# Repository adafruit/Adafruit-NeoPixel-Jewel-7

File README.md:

# Adafruit NeoPixel Jewel containing 7 NeoPixels

<a href="http://www.adafruit.com/products/2226"><br/>
Click here to purchase one from the Adafruit shop</a>

We fit seven of our tiny 5050 (5mm x 5mm) smart RGB LEDs onto a beautiful, round PCB with mounting holes and a chainable design to create what we think is our most elegant (and evening-wear appropriate) NeoPixel board yet.

Use only one microcontroller pin to control as many as you can chain together! Each LED is addressable as the driver chip is inside the LED. Each one has ~18mA constant current drive so the color will be very consistent even if the voltage varies, and no external choke resistors are required making the design slim. Power the whole thing with 5VDC and you're ready to rock.

PCB files for Adafruit NeoPixel Jewel with 7 NeoPixel LEDs

For more details, check out the product page at

-----> https://www.adafruit.com/product/2226

### License

Adafruit invests time and resources providing this open source design, please support Adafruit and open-source hardware by purchasing products from [Adafruit](https://www.adafruit.com)!

All text above must be included in any redistribution

Designed by Limor Fried/Ladyada for Adafruit Industries.
Creative Commons Attribution/Share-Alike, all text above must be included in any redistribution. 
See license.txt for additional information.

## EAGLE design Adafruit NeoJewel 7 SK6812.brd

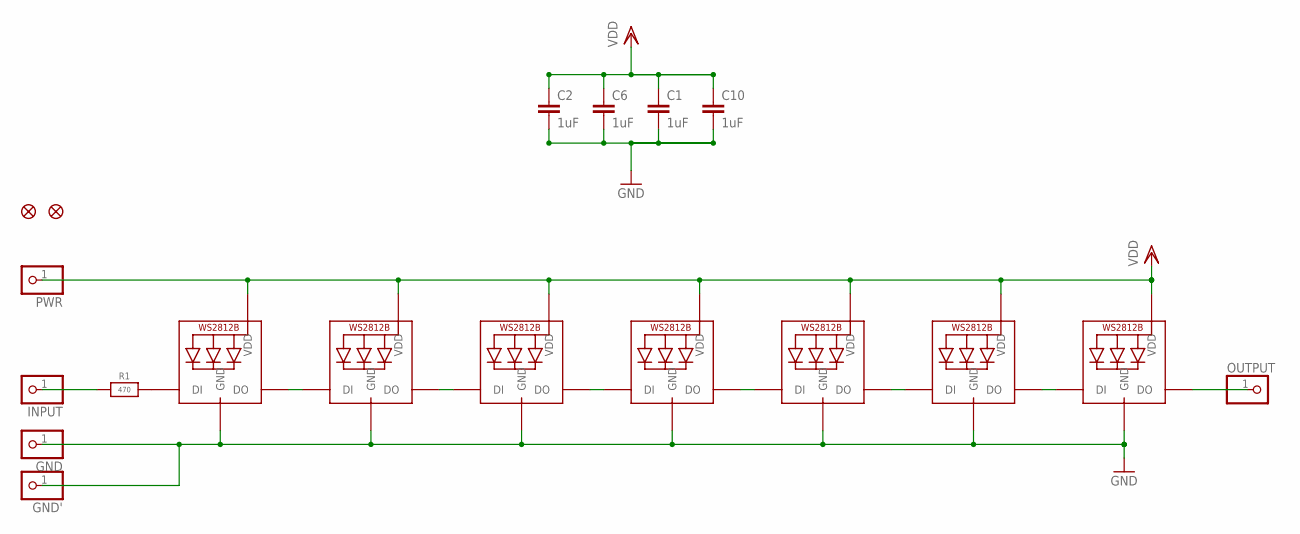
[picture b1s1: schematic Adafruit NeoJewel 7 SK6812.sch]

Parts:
C1, C2, C6, C10: 1uF; C0603
FID1, FID2: FIDUCIAL_1MM
GND: PINHD-1X1CB; 1X01-CLEANBIG
GND': PINHD-1X1CB; 1X01-CLEANBIG
INPUT: PINHD-1X1CB; 1X01-CLEANBIG
LED1, LED2, LED3, LED4, LED5, LED6, LED7: WS2812B_5050N; WS2812B-NARROW
OUTPUT: PINHD-1X1CB; 1X01-CLEANBIG
PWR: PINHD-1X1CB; 1X01-CLEANBIG
R1: 470; 0603-NO

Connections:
GND: C1.2, C2.2, C6.2, C10.2, GND.1, GND'.1, LED1.3-GND (GND), LED2.3-GND (GND), LED3.3-GND (GND), LED4.3-GND (GND), LED5.3-GND (GND), LED6.3-GND (GND), LED7.3-GND (GND)
unnamed: LED1.2-DOUT (DO), LED2.4-DIN (DI)
unnamed: LED2.2-DOUT (DO), LED3.4-DIN (DI)
unnamed: LED3.2-DOUT (DO), LED4.4-DIN (DI)
unnamed: LED4.2-DOUT (DO), LED5.4-DIN (DI)
unnamed: LED5.2-DOUT (DO), LED6.4-DIN (DI)
unnamed: LED6.2-DOUT (DO), LED7.4-DIN (DI)
unnamed: LED7.2-DOUT (DO), OUTPUT.1
unnamed: LED1.4-DIN (DI), R1.2
unnamed: INPUT.1, R1.1
VDD: C1.1, C2.1, C6.1, C10.1, LED1.1-VDD (VDD), LED2.1-VDD (VDD), LED3.1-VDD (VDD), LED4.1-VDD (VDD), LED5.1-VDD (VDD), LED6.1-VDD (VDD), LED7.1-VDD (VDD), PWR.1

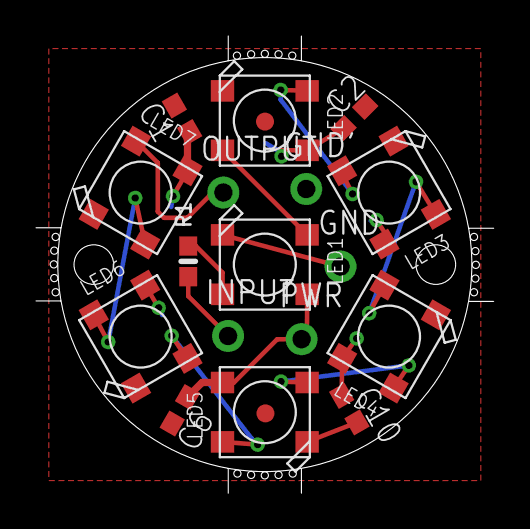
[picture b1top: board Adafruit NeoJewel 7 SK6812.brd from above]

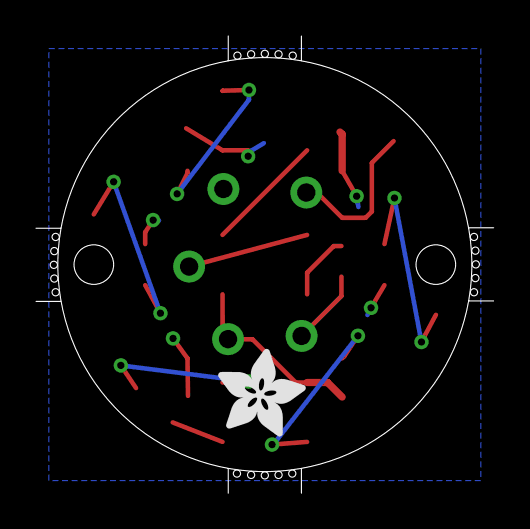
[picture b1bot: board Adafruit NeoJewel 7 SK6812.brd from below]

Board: 2 copper layers, 23.0 x 23.0 mm, 30 parts (7 on the bottom side), 11 nets.

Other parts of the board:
PLABEL0: PLABEL0
PLABEL1: PLABEL1
PLABEL2: PLABEL2
PLABEL3: PLABEL3
PLABEL4: PLABEL4
PLABEL5: PLABEL5
PLABEL6: PLABEL6
PLABEL7: PLABEL7
PLABEL8: PLABEL8
PLABEL9: PLABEL9
U$3: ADAFRUIT_5MM

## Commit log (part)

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2015-01-19 init

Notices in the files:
parts and their libraries:
microbuilder: This work is placed in the public domain, and may be freely used for commercial and non-commercial work with the following conditions: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
